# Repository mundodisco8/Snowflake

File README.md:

View this project on [CADLAB.io](https://cadlab.io/project/26393).

# Snowflake

A Snowflake Christmas decoration.

Just a design exercise, aiming to get a hand-solderable board (although a bit challenging) that blinks its LEDs without using a microcontoller. I guess you can call it a mix of digital and analogue electronics, because the main trigger is a binary counter that is fed by a clock generated with an opamp in astable multivibrator config.

## Outputs

The outputs of this project can be found in the Releases area.

## Documentation

### Design Intention

You can find the design document in the [docs section](docs/Design%20Justification.ipynb), as a Jupyter notebook, or [better rendered here](https://mundodisco8.github.io/Snowflake), as a static rendering of the jupyter notebooks. For an interactive session, you can launch it on Binder if you want to play with the sliders.

You might even want to clone this repo and get your hands dirty. If you do, remember to create a virtual environment and install all the requirements.

```bash
python -m venv venv
venv/Scripts/Activate.bat # or source venv/bin/activate in Linux/Mac
python -m pip install -r requirements.txt
```

### Other bits and bobs

In the LTSpice folder you will find the circuits used on the Jupyter notebook to guess the current consumption as the battery discharges.

The `docs` folder also contains a couple of Excel spreadsheets I used to calculate some stuff, but they are not that interesting.

## Support Folder

The support folder contains random stuff that I needed at some point, mostly graphics.

I nicked the graphics from [here](https://svgsilh.com/image/2960229.html), which in turn is a variation of [this](https://pixabay.com/illustrations/snowflake-pattern-decor-decorative-2960229/).

## Running the CI/CD locally

The Release section only contains the artifacts of some hand-picked commits. Github Actions run on each commit on master, but the artifacts generated there have a self-life and get deleted after 15 days, I think. If you want, you can run the CICD pipeline locally.

```bash
# on the folder containing the project
# pull the KiBot image
docker pull ghcr.io/inti-cmnb/kicad7_auto_full:dev
# create a container named KiBotSnowDev, attaching the current folder as /Snowflake
docker run -it --name KiBotSnowDev -v .:/SnowFlake --entrypoint=/bin/bash ghcr.io/inti-cmnb/kicad7_auto_full:dev
# Now you are attached to the container
kibot -c ArtifactCreation.kibot.yaml -e hardware/Snowflake.kicad_sch -b hardware/Snowflake.kicad_pcb
```

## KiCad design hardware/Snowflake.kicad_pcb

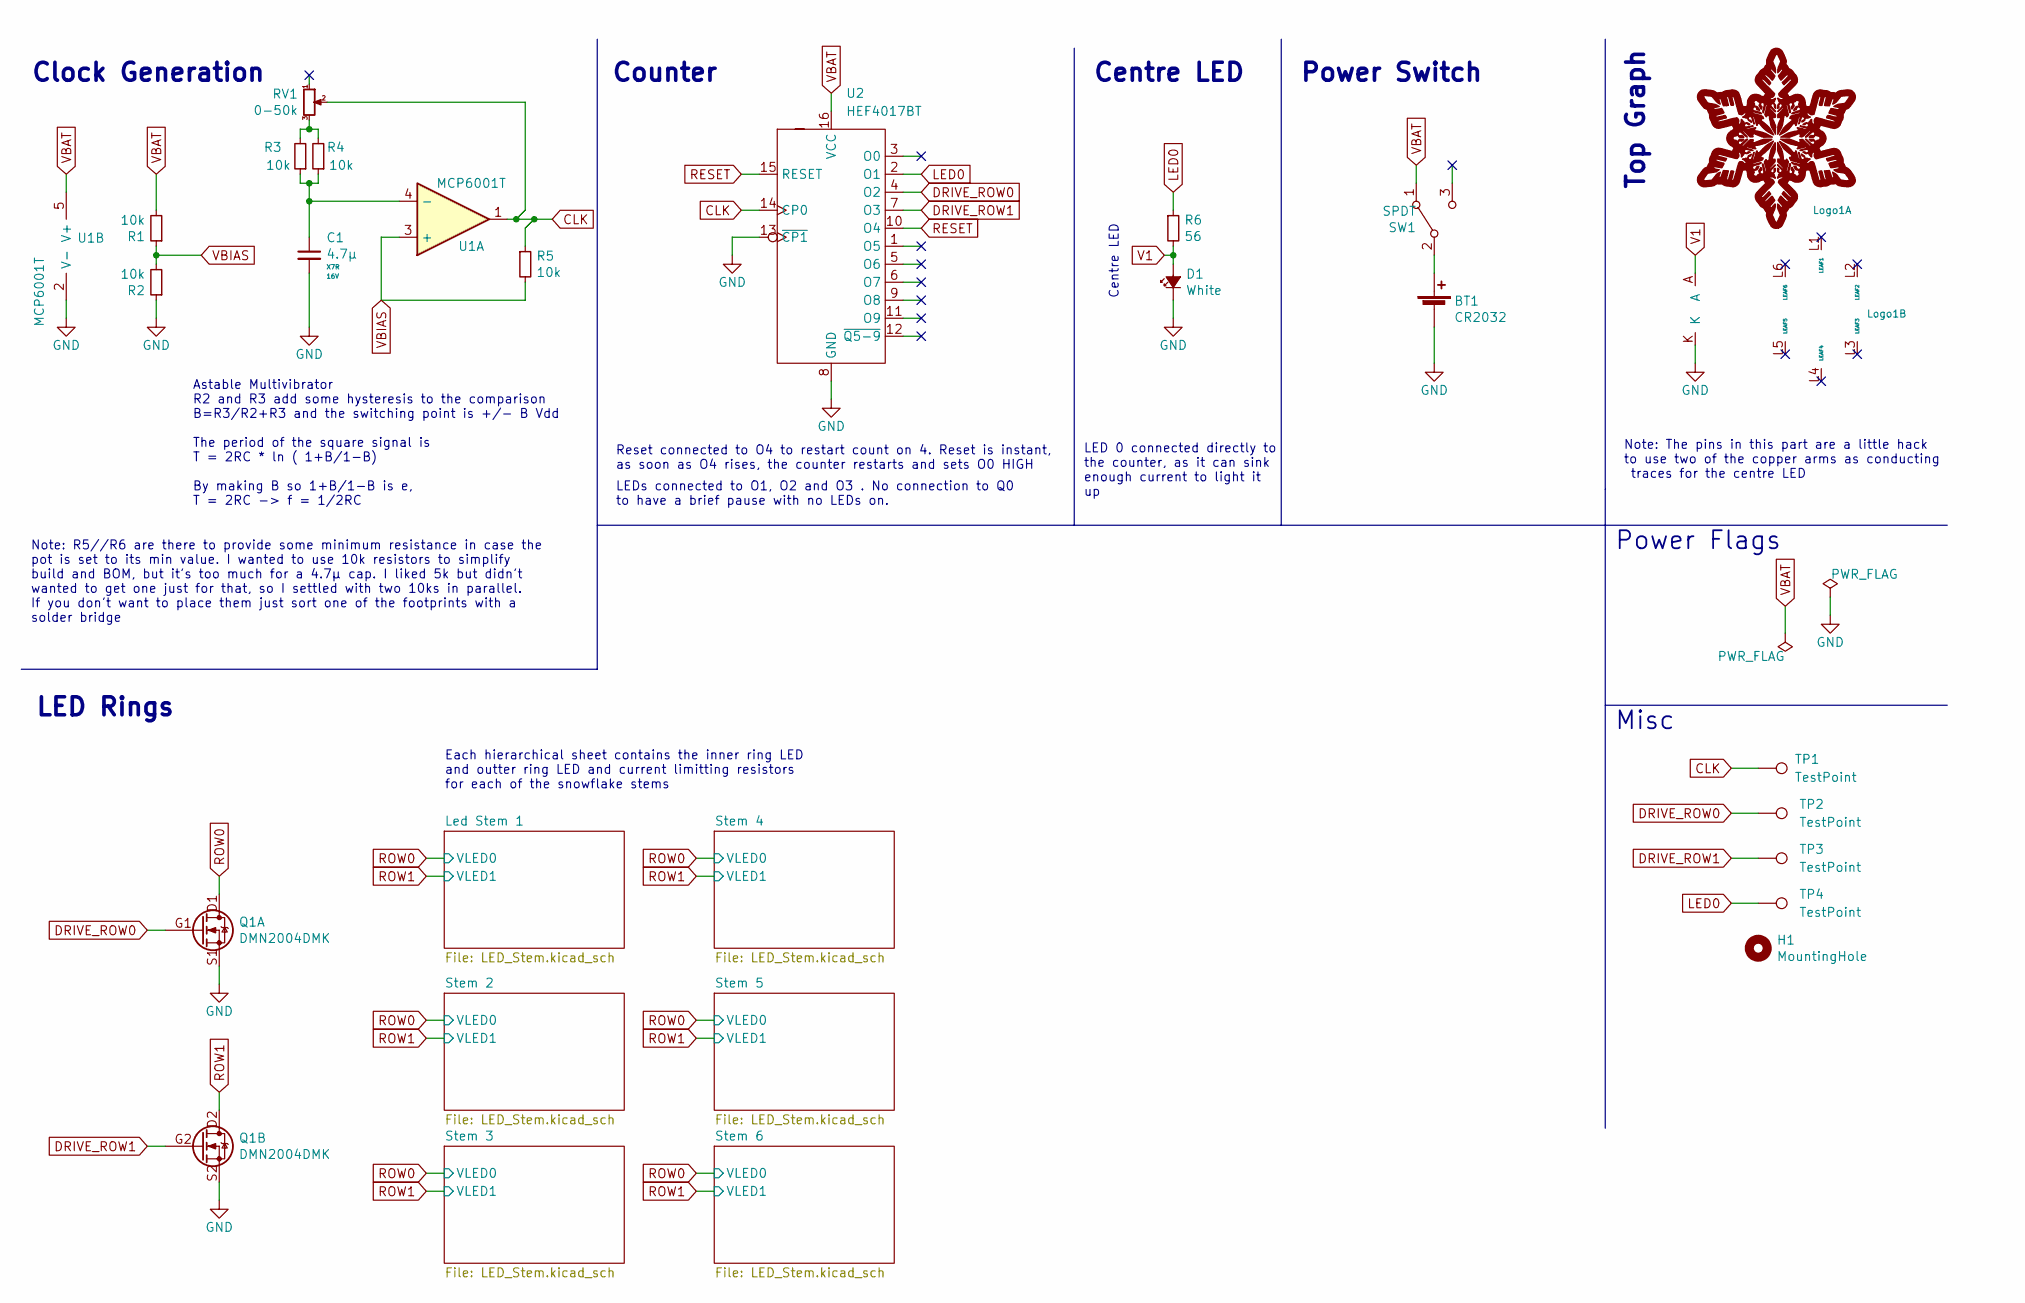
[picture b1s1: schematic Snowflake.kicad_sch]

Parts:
BT1: CR2032; CR2032_Keystone_3034; MPN 3034; Digikey PN 36-3034-ND
C1: 4.7μ; 0805-C_Handsolder_NoSilk; Tolerance ±10%; MPN GRM21BR71C475KE51K; Digikey PN 490-GRM21BR71C475KE51KCT-ND
D1: White; 3014_LED_HandSolder_NoSilk; MPN KWDCLMS2.EC-CXCZ-4L7M; Digikey PN 475-KWDCLMS2.EC-CXCZ-4L7M-1-20-R18CT-ND
H1: MountingHole; MountingHole_2.1mm_M2; MPN N/A; Digikey PN N/A
Logo1: Snowflake; MPN N/A; Digikey PN N/A
Q1: DMN2004DMK; SOT-23-6_DMN2004DMK_Handsoldering_NoSilk; MPN DMN2004DMK; Digikey PN DMN2004DMKDICT-ND
R1, R2, R3, R4, R5: 10k; 0805-R_Handsolder_NoSilk; Tolerance ±1%; MPN AF0805FR-0710KL; Digikey PN 13-AF0805FR-0710KLCT-ND
R6: 56; 0805-R_Handsolder_NoSilk; Tolerance ±1%; MPN RC0805FR-1056RL; Digikey PN 311-56ARCT-ND
RV1: 0-50k; Potentiometer_TC33X-2-204E_NoSilk; Tolerance ±25%; MPN TC33X-2-503E; Digikey PN TC33X-503ECT-ND
SW1: SPDT; Slider_Switch_C&K_AYZ0102AGRLC_SPDT_RightAngle_NoSilk; MPN AYZ0102AGRLC; Digikey PN 401-2012-1-ND
TP1, TP2, TP3, TP4: TestPoint; TestPoint_Pad_D1.0mm_NoSilk
U1: MCP6001T; Op_Amp_SOT23_MCP6001T_NoSilk; MPN MCP6001T-I/OT; Digikey PN MCP6001T-I/OTCT-ND
U2: HEF4017BT; 16-SOIC_3.9x9.9mm_P1.27mm_NoSilk; MPN HEF4017BT,653; Digikey PN 1727-6402-1-ND

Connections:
CLK: R5.1, RV1.2, TP1.1, U1.1, U2.14 (CP0)
DRIVE_ROW0: Q1.G1, TP2.1, U2.4 (O2)
DRIVE_ROW1: Q1.G2, TP3.1, U2.7 (O3)
GND: BT1.2 (-), C1.2, D1.K, Logo1.K, Q1.S1, Q1.S2 (S1), R2.1, U1.2 (V-), U2.8 (GND), U2.13 (~CP1)
LED0: R6.1, TP4.1, U2.2 (O1)
unnamed: BT1.1 (+), SW1.2 (B)
unnamed: R3.2, R4.2, RV1.3
unnamed: C1.1, R3.1, R4.1, U1.4 (-)
RESET: U2.10 (O4), U2.15 (RESET)
ROW0: Q1.D1; also elsewhere on the board
ROW1: Q1.D2 (D1); also elsewhere on the board
V1: D1.A, Logo1.A, R6.2
VBAT: R1.2, SW1.1 (A), U1.5 (V+), U2.16 (VCC); also elsewhere on the board
VBIAS: R1.1, R2.2, R5.2, U1.3 (+)

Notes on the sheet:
Top Graph
Clock Generation
Power Flags
Misc
Counter
Power Switch
Centre LED
Note: The pins in this part are a little hack to use two of the copper arms as conducting traces for the centre LED
Reset connected to O4 to restart count on 4. Reset is instant, as soon as O4 rises, the counter restarts and sets O0 HIGH
Each hierarchical sheet contains the inner ring LED and outter ring LED and current limitting resistors for each of the snowflake stems
LED Rings
Astable Multivibrator R2 and R3 add some hysteresis to the comparison B=R3/R2+R3 and the switching point is +/- B Vdd The period of the square signal is T = 2RC * ln ( 1+B/1-B) By making B so 1+B/1-B is e, T = 2RC -> f = 1/2RC
Centre LED
LEDs connected to O1, O2 and O3 . No connection to Q0 to have a brief pause with no LEDs on.
Note: R5//R6 are there to provide some minimum resistance in case the pot is set to its min value. I wanted to use 10k resistors to simplify build and BOM, but it's too much for a 4.7μ cap. I liked 5k but didn't wanted to get one just for that, so I settled with two 10ks in parallel. If you don't w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
LED 0 connected directly to the counter, as it can sink enough current to light it up

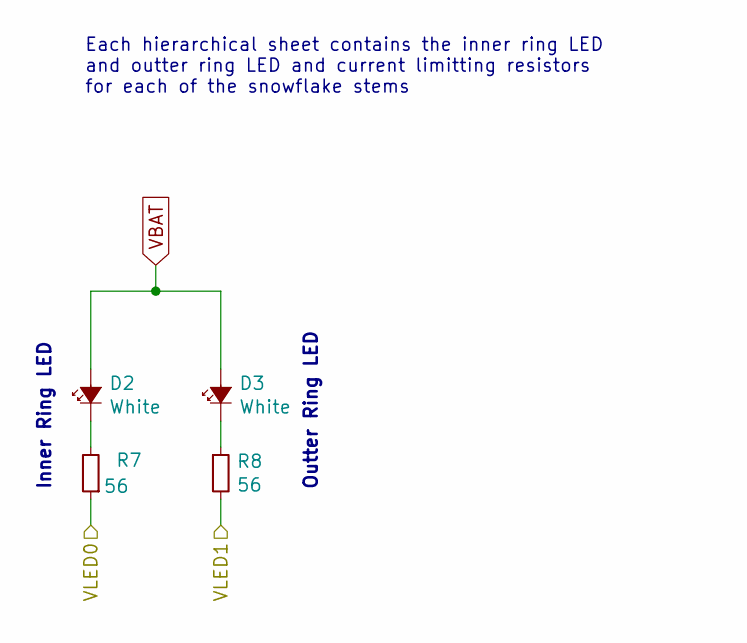
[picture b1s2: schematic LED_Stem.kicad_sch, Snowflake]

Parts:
D2, D3: White; 3014_LED_HandSolder_NoSilk; MPN KWDCLMS2.EC-CXCZ-4L7M; Digikey PN 475-KWDCLMS2.EC-CXCZ-4L7M-1-20-R18CT-ND
R7, R8: 56; 0805-R_Handsolder_NoSilk; Tolerance ±1%; MPN RC0805FR-1056RL; Digikey PN 311-56ARCT-ND

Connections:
unnamed: D2.K, R7.2
unnamed: D3.K, R8.1
ROW0: R7.1; also elsewhere on the board
ROW1: R8.2; also elsewhere on the board
VBAT: D2.A, D3.A; also elsewhere on the board

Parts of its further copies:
D4, D5, D6, D7, D8, D9, D10, D11, D12, D13: White; 3014_LED_HandSolder_NoSilk; MPN KWDCLMS2.EC-CXCZ-4L7M; Digikey PN 475-KWDCLMS2.EC-CXCZ-4L7M-1-20-R18CT-ND
R9, R10, R11, R12, R13, R14, R15, R16, R17, R18: 56; 0805-R_Handsolder_NoSilk; Tolerance ±1%; MPN RC0805FR-1056RL; Digikey PN 311-56ARCT-ND

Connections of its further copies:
unnamed: D4.K, R9.2
unnamed: D5.K, R10.1
unnamed: D6.K, R11.2
unnamed: D7.K, R12.1
unnamed: D8.K, R13.2
unnamed: D9.K, R14.1
unnamed: D10.K, R15.2
unnamed: D11.K, R16.1
unnamed: D12.K, R17.2
unnamed: D13.K, R18.1
ROW0: R9.1, R11.1, R13.1, R15.1, R17.1; also elsewhere on the board
ROW1: R10.2, R12.2, R14.2, R16.2, R18.2; also elsewhere on the board
VBAT: D4.A, D5.A, D6.A, D7.A, D8.A, D9.A, D10.A, D11.A, D12.A, D13.A; also elsewhere on the board

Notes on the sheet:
Outter Ring LED
Inner Ring LED
Each hierarchical sheet contains the inner ring LED and outter ring LED and current limitting resistors for each of the snowflake stems

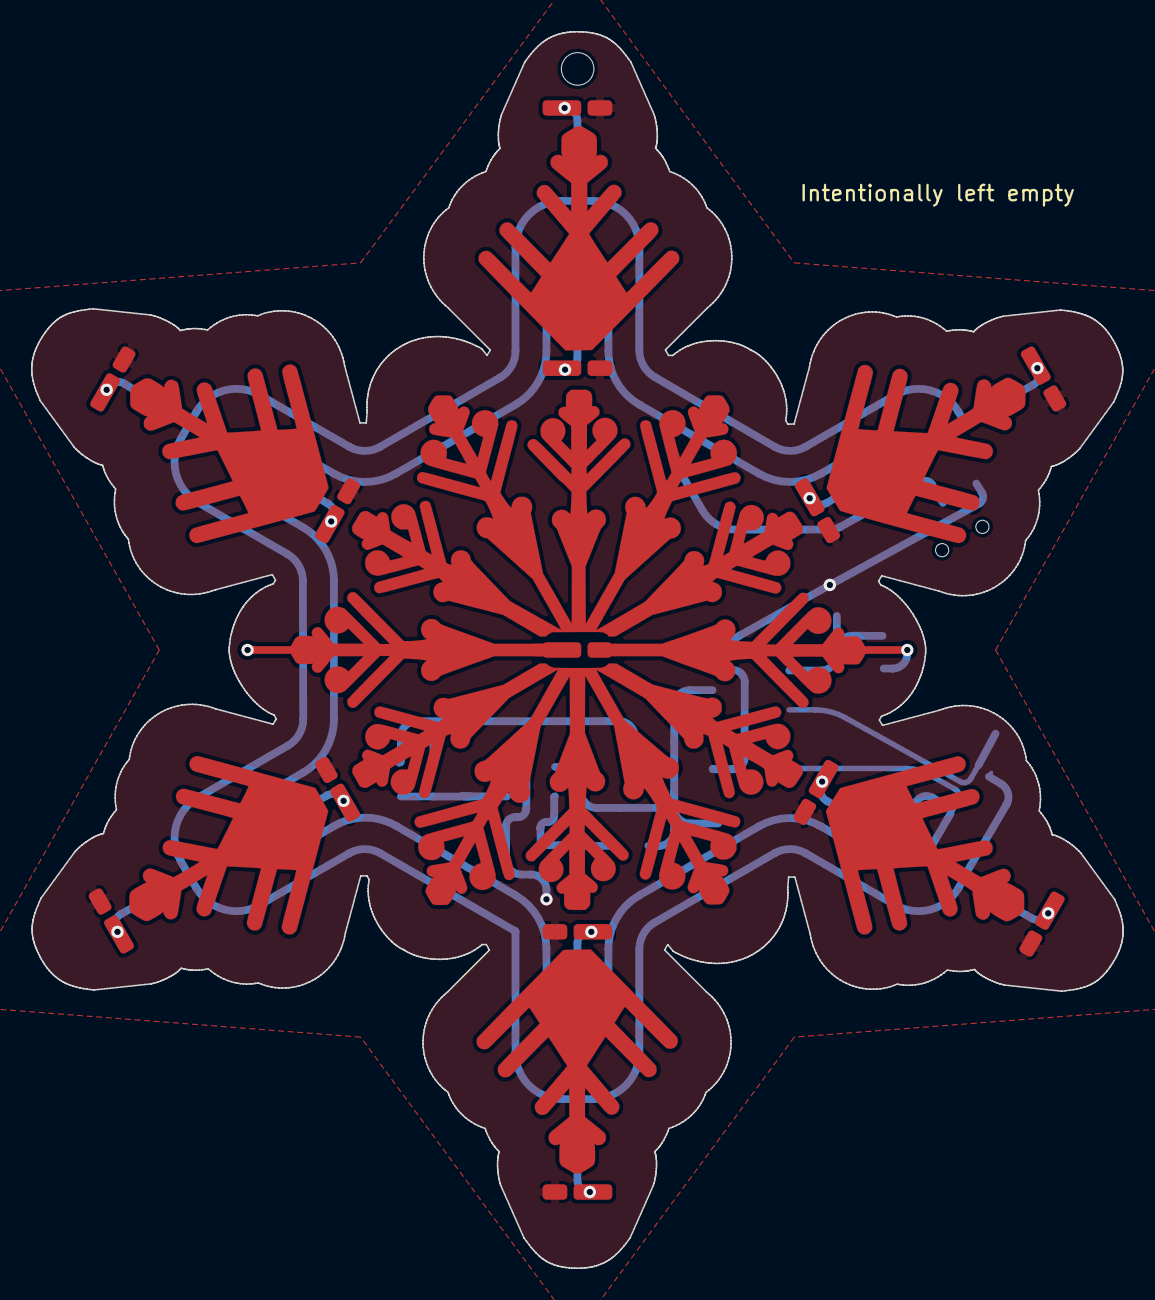
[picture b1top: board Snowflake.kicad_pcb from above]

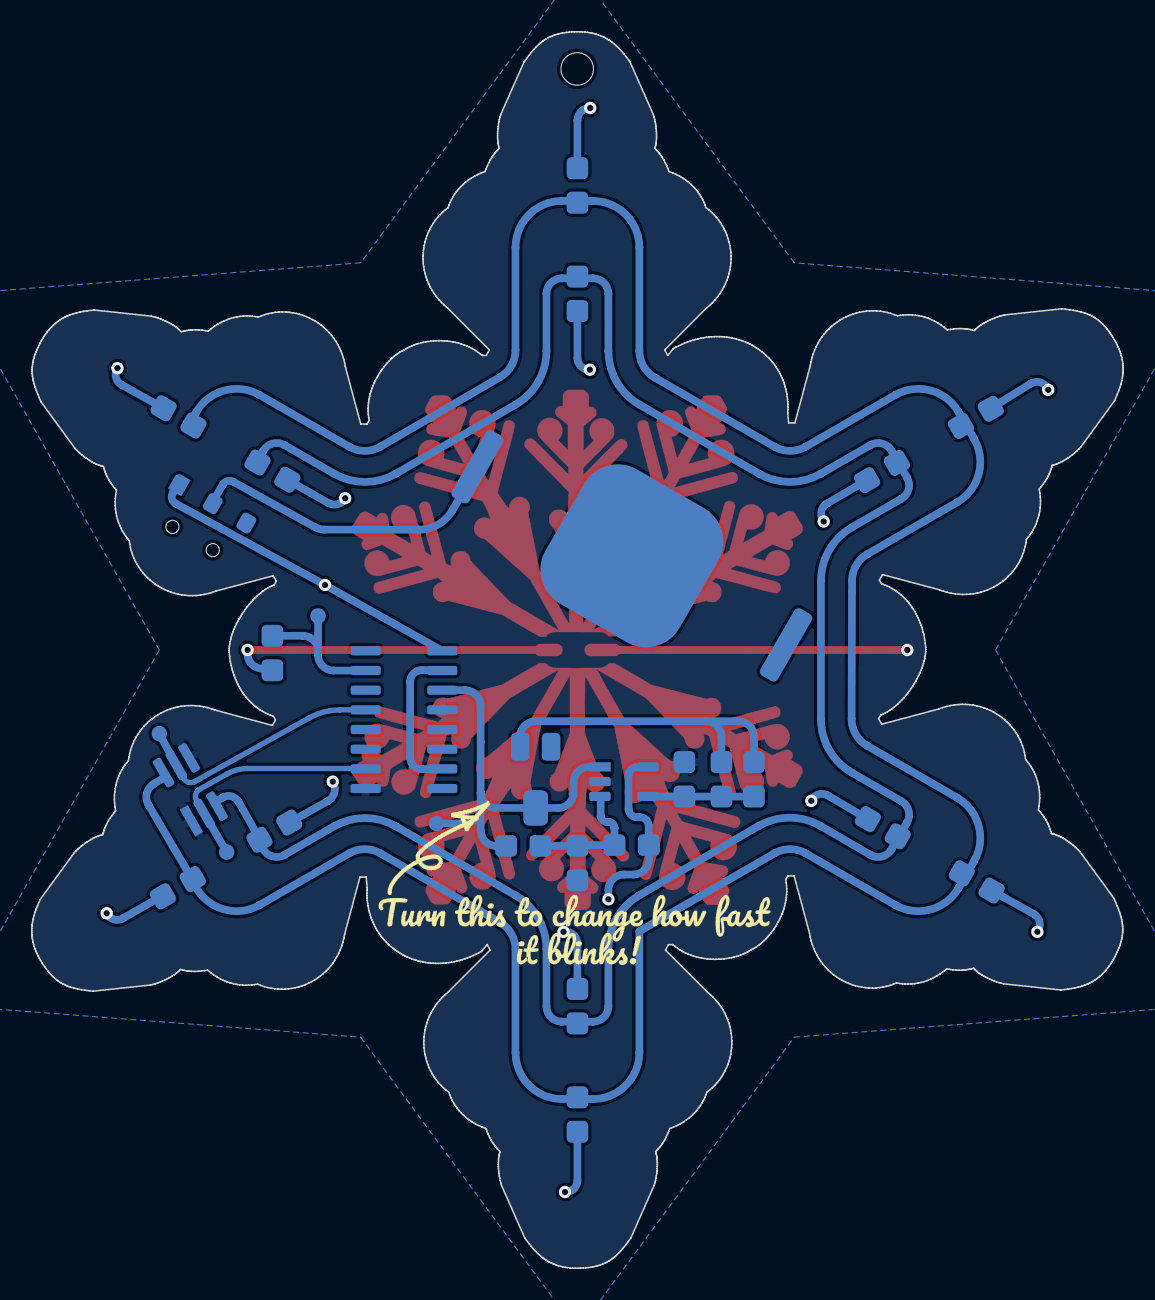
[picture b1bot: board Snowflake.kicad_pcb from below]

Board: 2 copper layers, 70.5 x 79.8 mm, 45 parts (30 on the bottom side), 26 nets.

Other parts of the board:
S1: Turn_This!

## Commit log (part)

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2019-11-14 First Commit Schematic is enough to start working. Need to add power
2019-11-15 Added battery holders
2019-12-03 Added the Snowflake part to the library
2019-12-06 Schematic 99%, just needs a couple of tweaks (assign footprints to the OpAmp and the switch) Added a bunch of 3D models and footprints
2019-12-06 Terayza new parts added and some layout started
2019-12-10 Terayza changes
2019-12-10 All footprints in place, schematic done
2019-12-11 Still leaft to connect: Vbat from all the LEDs
2019-12-11 A bit of tidying up in the PCB.
2019-12-19 Test
2020-01-14 Rerouter the tracks in 30 degrees
2020-01-14 Added some files to the support folder
2020-01-14 Added render to project
2022-09-16 Updated the Design to KiCad6 and made the track corners rounded
2022-09-20 Updated Symbol Library to KiCad 6 Removed Silk from LEDs on front Added six extra pads to the snowflake
2022-09-20 Fixed a bug, where I was sorting all the LEDs :S Removed all DRC rules Ready to fillet tracks
2022-09-20 Rounded the tracks!
2022-10-03 Discarded the idea of using AAA batteries and switched to CR2032s
2022-10-12 Pre-test push. Happy with the layout, waiting for the tests to choose an LED, resitor and battery holder
2022-10-19 Happy with the HW
2022-10-19 Created a venv for jupyter
2022-10-19 Documentation in a Jupyter Notebook
2022-10-25 Added Voila and requirements.txt
2022-10-25 updated the gitignore and removed a shit ton of files
2022-11-09 Updated footprint for LED as it was a bit off and changed to a single CR2032 holder that's quite compact
2022-11-09 Configured KIBoM as BoM manager
2022-11-09 Changed a couple of parts to alternatives that are more available AND cheaper
2022-11-09 The switch had lost its 3D Model
2023-01-06 v1.0.0 First manufactured version Updated gitignore and removed a bunch of virtualenv files Tweaked some footprints Added farnell PN, MPNs, etc.
2023-01-06 Added a reference to the silkscreen element (it was the default REF**)
2023-01-10 Fixed some DRCs introduced on KiCad 6.0.10 (changes in the PWR symbol library)
2023-01-11 Added some text to the sheet to commit hash and date printed on the outputs
2023-01-11 first commit with github actions
2023-01-11 Updated CICD
2023-01-11 k2v6
2023-01-12 CICD is working on Github, last touches to files before work on v1.1.0 starts
2023-01-16 Backlink to CADLAB.io has been added.
2023-01-27 Added Assembly Instructions output
2023-01-29 Fixed Typo in KiBot config
2023-01-29 Updated Github Actions versions to remove deprecation warning
2023-10-06 Some changes in the project to get it to pass in the latest KiBot docker image
2023-10-08 Changed the Counter footprint to 16-SOIC
2023-10-12 Updated CI/CD, split config in multiple files so it's easy to keep track of everything Added an action that updates the images used in the readme and pushes them back to the repo.
2023-10-12 Continuous Integration Build Artifacts
2023-10-12 updated the gitignore and removed a shit ton of files
    (cherry picked from commit 2ac760f120fdc4ab050bc348e730def5f6d87db7)
2023-10-15 Light edition of the notebook. Created requirements.txt Removed Voila, as it's not needed to build the notebook-as-a-page
2023-10-16 Venv files cleanup
2023-10-17 First config for Jupyter Books.
2023-10-17 Testing github actions
2023-10-17 deploy: fc7f0e5d930d3663557aa9135d7a26d6fe4dfbff
2023-10-17 Github Actions publish 2
2023-10-17 remove whitespaces just in case
2023-10-17 deploy: 620e0d2ccbcca0ff5892b2dc6e1a08a83dc685a8
2023-10-17 Adding interactive support to binder
2023-10-17 quote
2023-10-17 deploy: 41175bd06235e4e55c7b6afe6225902d466a13e8
2023-10-18 Added postbuild step for binder
2023-10-18 Ready to merge
2023-10-18 deploy: 5f3476c4198343e09c4f85baf3f514f961175608
2023-10-19 Closed remaining issues in Github (#10, #7, #6, #3) * Tweaked the SOT23-6 footprint * Tweaked the rotary pot footprint * Tweaked the LED footprint * Added some testpoints
2023-10-19 Fixed errors on CICD
2023-10-19 Froze the python requirements
2023-11-08 Added some stuff missing from the BoM Changed the LED component name from 4014 to 3014 (typo). Updated schematic and board
2023-11-08 Fix CI/CD warning
